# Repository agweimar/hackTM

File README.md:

# HackTM 2018 project #smucl

[Hardware overview](#hardware)

[Quickstart](#quickstart)

[Micropython](#mpython)

## Hardware overview 
The sensor board/shield holds three major components, namely:
* ESP32 breakout board with LoRa antenna and OLED display
* Flex Cable including I2C addressable Sensirion SHTC01 (rel. humidity and temperature) and SGP30 (multipixle gas sensor)
* Passive infrared sensor (PIR) a.k.a. motion sensor

A top view of the board is shown below:

### ESP32 development board 

The ESP32 breakout board is put in the socket on the lower left of the board. The usb port is facing outwards, so the board can be powered from an external (USB) power supply.
On the bottom side of the ESP32 board a small LiPo battery can be connected. Charging this battery takes place via the USB port.  
_Caution_: When booting or running the board the LoRa antenna must be connected!  
[Schematic](https://download.bastelgarage.ch/Datasheet/WIFI_LoRa_32_868_Schema.png)
[Pinout](https://download.bastelgarage.ch/Datasheet/WIFI_LoRa_32_Pinout.pdf)

### Flex cable  
The flex cable is put in the FFC socket above the ESP32 board. It is to be mounted in such a fashion, that the sensors face upwards when the cable is bent to the right (parallel to the ESP32 board).  
The flex cable combines the Sensirion SHTC1 and SGP30. Both of the sensors are accessed via I2C. The former is a sensor for relative humidity and temperature, the latter a multipixle gas sensor.  
For both sensors a convenient micropython driver can be found in the micropython directory. 

#### SGP30  
The SGP30 can give raw readings corresponding to an Ethanol (EtOH) and Hydrogen (H2) signal. However, this chip can do more! If an In-Air-Qualitiy measurement has been initialized, the raw signals are used to calculate  
the a TVOC signal (total volatile organic compounds) and an CO2 equivalent (CO2eq). These values already underly a dynamic baseline correction performed on-chip. To ensure these corrections works properly, it is advised to perform an iaq measurement once per second.  
The power consumption of the chip can be drastically minimized by soft resetting it. This is done by an i2c general call. Caution is adviced, since other i2c devices might respont to this call as well. After each reset (hard or soft) the sensor starts in idle or sleep mode with lower power consumption. If a new iaq measurement is of intereset it needs to be initialized first,
otherwise the default values are CO2eq = 400 and TVOC = 0.  
For additional information see the below datasheet.  
[SGP30 Datasheet](https://www.sensirion.com/fileadmin/user_upload/customers/sensirion/Dokumente/0_Datasheets/Gas/Sensirion_Gas_Sensors_SGP30_Datasheet.pdf)  

#### SHTC1  
The SHTC1 sensor is a little simpler than the SGP30. It gives values for temperature and relative humidity. The sensor can be soft reseted, but doesn't have a sleep mode due to its already low power consumption.
[SHTC1 Datasheet](https://www.sensirion.com/fileadmin/user_upload/customers/sensirion/Dokumente/0_Datasheets/Humidity/Sensirion_Humidity_Sensors_SHTC1_Datasheet.pdf)  
Side note: The Sensirion sensors are powered with 1.8V. The electrical components taking care of voltage generation and conversion (for the I2C bus, including 10k pull-up resistors) are situated on the bottom side of the sensor board - see picture below:

### PIR
The PIR sensor is placed on the right side of the sensor board. It produces a digital Signal (logic high) whenever a motion was detected. The sensor is internally powered by 3.3V. This voltage is generated on the PIR board by a voltage regulator.
The solder jumper labeled 'V_In' on the right side selects the input voltage - either 5V or 3.3V. Keep in mind that the 5V is only 'stable' when powered via USB.
Another (prefered and thus default) way to power the PIR Board is the second socket strip on the lower side. Originally those pins are designed to select the trigger mode (explained later). However, the outer two pins are connected to ground and 3.3V of the PIR sensor.
This enables the option to surpass the PIR's voltage regulator and save energy by directly supplying 3.3V.  
Via the solder jumpers labelled 'Single Trigger' and 'Retrigger' it can be selected if retriggering is possible. Retriggering is the possibility of increasing the duration of the digital output signal, when additional motion(s) are detected.
If 'Single Trigger' is selected the output signal will return to its default state () when a certain time has passed after detecting the first motion. Only now new motions cann trigger the sensor. The pulse length of the output signal can be selected with the left (when mounted upper) trimmable potentiometer.
The right (when mounted lower) potentiometer adjusts the sensitivity of the PIR sensor.  
[Example Datasheet](https://www.mpja.com/download/31227sc.pdf)
[Trigger Explanation](http://www.ladyada.net/media/sensors/BISS0001.pdf)

## Extras  
In addition to the previously mentioned features extra pins can be found on the sensor board. These are broken out pins (as well as solder eyelets) to conveniently expand the board.
They include the power pins (5V, 3.3V and GND - 5V may be limited to USB use) as well as the I2C pins SDA and SCL (3.3V level). Furthermore 4 GPIOs are broken out. Those can be used for a wide variety of scenarios.
All of them can be configured via software to be digital or analogue for different I/O devices. These pins could also be used as an SPI bus.

## Quickstart ESP32  

The ESP32 can be programmed using the Ardunio IDE, the Internet-of-Things Framework from Espressif or using [Micropython](https://micropython.org/). We chose Micropython, because it is very easy to start with and the code is very readable even for coders that are new to python.
Of course you can use your favourite IDE or even a simple text editor to code. However, below are a few suggestions of tools, that could make your life much easier.  

## Micropython  
In order to start with changing the sources for your needs, start looking in [micropython](micropython)

You can copy files to and from the board using different libaries:

### mpy utils  
[mpy-utils](https://github.com/nickzoic/mpy-utils) establishes a Filesystem in userspace connection to the board and allow you to change files directly on the board. (very handy)bla
_doesn't work on Windows_

### ampy
[ampy](https://github.com/adafruit/ampy) is used to interact with your esp32 board via serial connection.

### Atom with Pymakr Plugin
[Atom](https://atom.io/) can be used with the Pymakr Plugin (see [here](https://docs.pycom.io/chapter/pymakr/installation/atom.html) for help). Now you can use the powerful REPL (_Read-Evaluate-Print-Loop_),
which greatly helps while debubbing or prototyping. You can also run a pre-written script with just a click of a button (without uploading first).

### esptool.py
[esptool](https://github.com/espressif/esptool) is needed for flashing your esp32 with new firmware.

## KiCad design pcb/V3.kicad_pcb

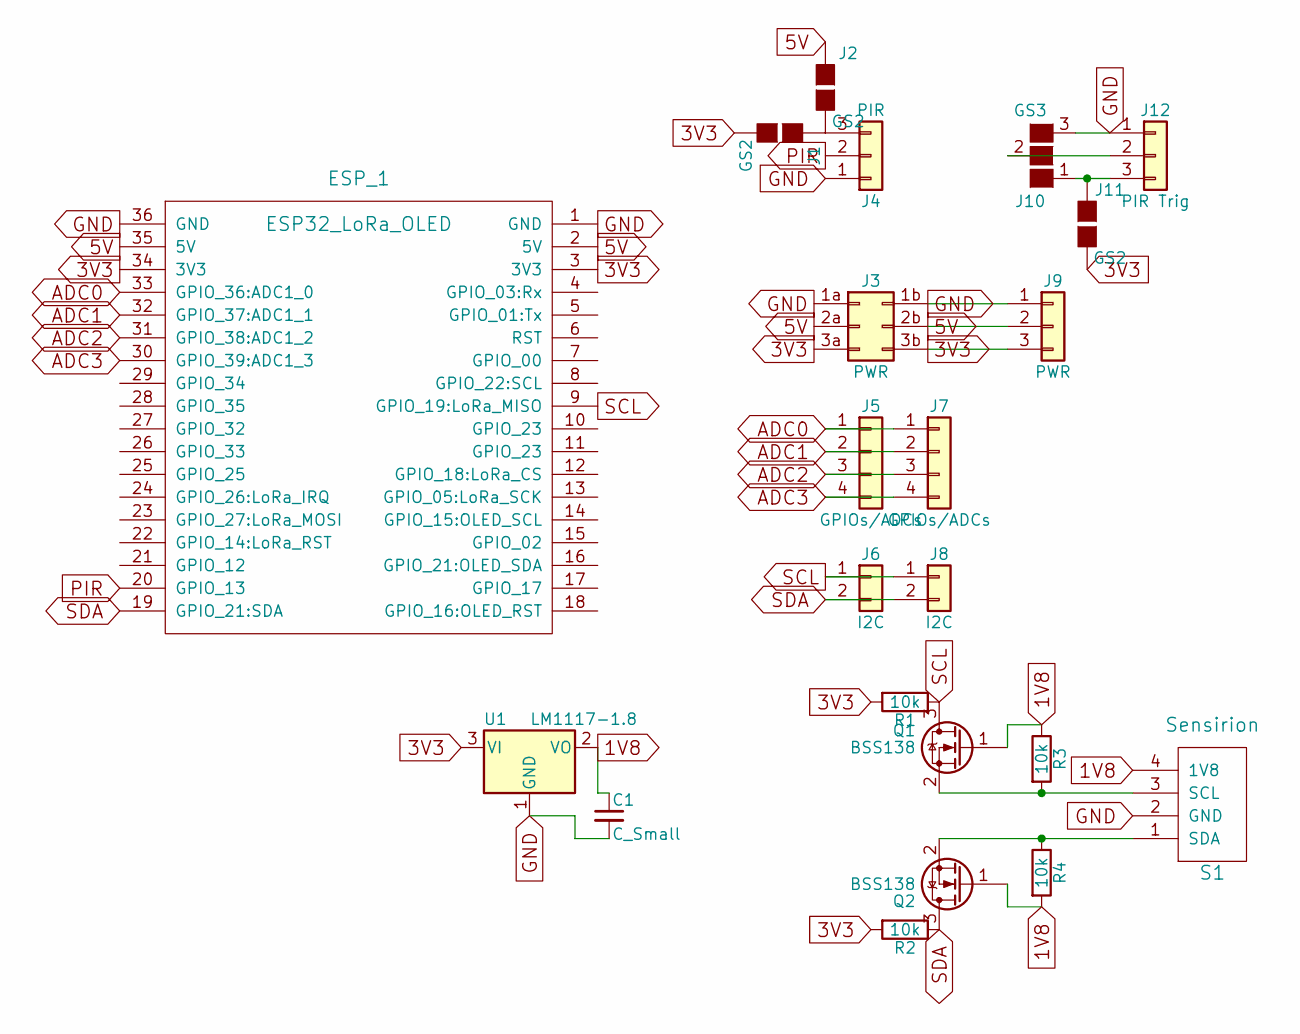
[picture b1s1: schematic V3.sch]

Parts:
C1: C_Small; C_1206_HandSoldering
ESP_1: ESP32_LoRa_OLED; ESP32_LoRa
J1, J2, J11: GS2
J3: PWR
J4: PIR; Pin_Header_Straight_1x03_Pitch2.54mm
J5, J7: GPIOs/ADCs; Pin_Header_Straight_1x04_Pitch2.54mm
J6, J8: I2C; Pin_Header_Straight_1x02_Pitch2.54mm
J9: PWR; Pin_Header_Straight_1x03_Pitch2.54mm
J10: GS3
J12: PIR Trig; Pin_Header_Straight_1x03_Pitch2.54mm
Q1, Q2: BSS138; SOT-23_Handsoldering
R1, R2, R3, R4: 10k; R_1206_HandSoldering
S1: Sensirion; FFC Amphenol
U1: LM1117-1.8; SOT-223-3_TabPin2

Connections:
1V8: C1.1, Q1.1 (G), Q2.1 (G), R3.1, R4.2, S1.4 (1V8), U1.2 (VO)
3V3: ESP_1.3 (3V3), ESP_1.34 (3V3), J1.2 (G2), J3.3a, J3.3b, J9.3, J11.2 (G2), R1.2, R2.2, U1.3 (VI)
5V: ESP_1.2 (5V), ESP_1.35 (5V), J2.1 (G1), J3.2a, J3.2b, J9.2
ADC0: ESP_1.33 (GPIO_36:ADC1_0), J5.1, J7.1
ADC1: ESP_1.32 (GPIO_37:ADC1_1), J5.2, J7.2
ADC2: ESP_1.31 (GPIO_38:ADC1_2), J5.3, J7.3
ADC3: ESP_1.30 (GPIO_39:ADC1_3), J5.4, J7.4
GND: C1.2, ESP_1.1 (GND), ESP_1.36 (GND), J3.1a, J3.1b, J4.1, J9.1, J10.3 (G3), J12.1, S1.2 (GND), U1.1 (GND)
unnamed: J1.1 (G1), J2.2 (G2), J4.3
unnamed: J10.1 (G1), J11.1 (G1), J12.3
unnamed: J10.2 (G2), J12.2
unnamed: Q1.2 (S), R3.2, S1.3 (SCL)
unnamed: Q2.2 (S), R4.1, S1.1 (SDA)
PIR: ESP_1.20 (GPIO_13), J4.2
SCL: ESP_1.9 (GPIO_19:LoRa_MISO), J6.1, J8.1, Q1.3 (D), R1.1
SDA: ESP_1.19 (GPIO_21:SDA), J6.2, J8.2, Q2.3 (D), R2.1

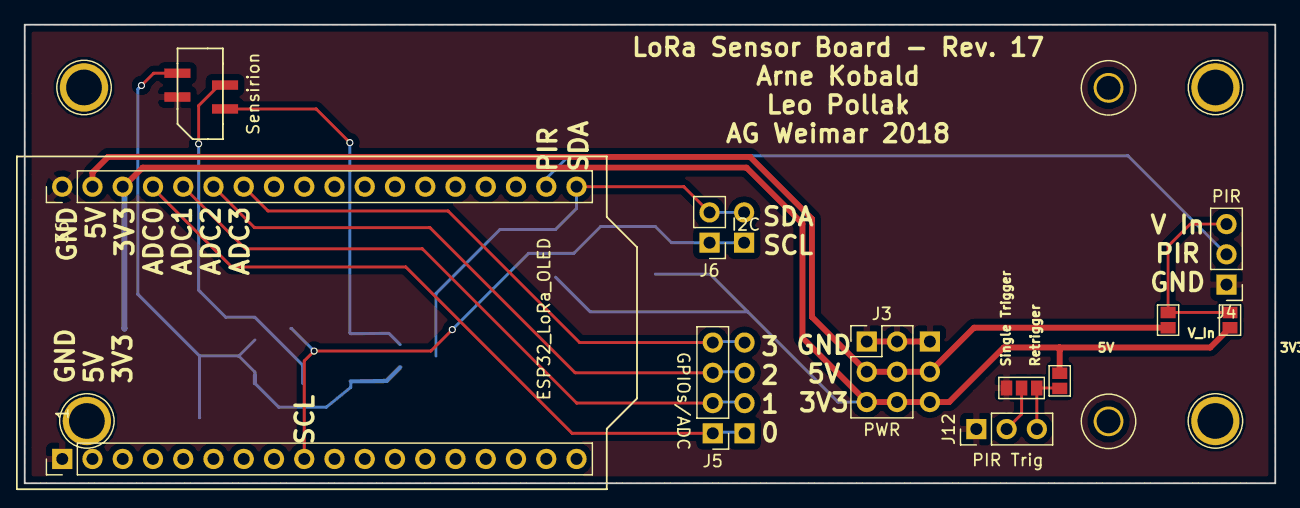
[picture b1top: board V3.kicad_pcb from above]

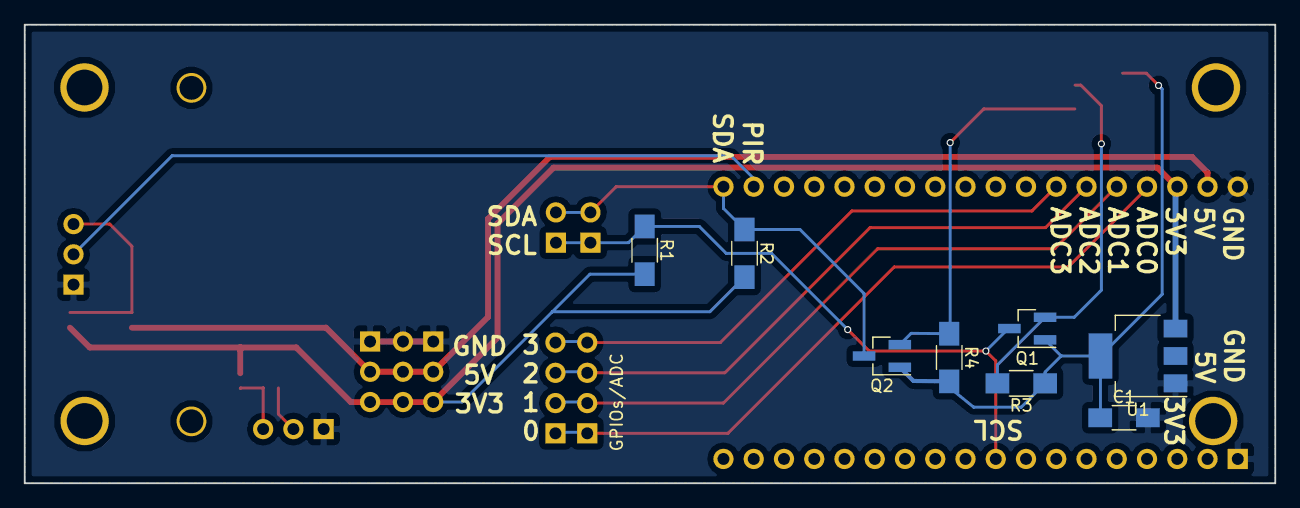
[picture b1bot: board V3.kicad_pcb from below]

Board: 2 copper layers, 105.0 x 38.5 mm, 22 parts (8 on the bottom side), 16 nets.

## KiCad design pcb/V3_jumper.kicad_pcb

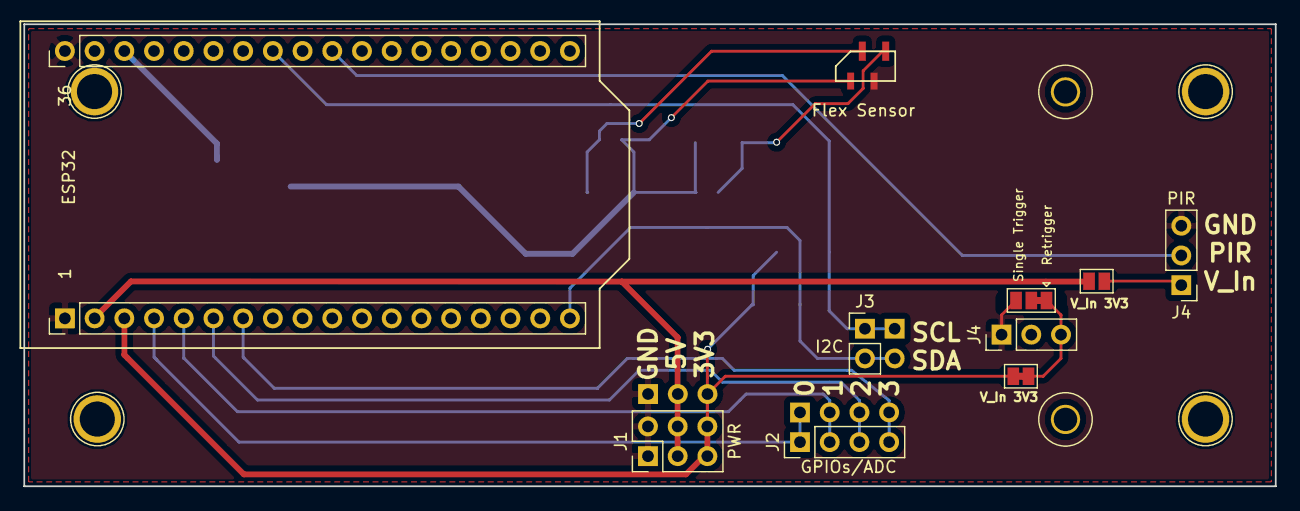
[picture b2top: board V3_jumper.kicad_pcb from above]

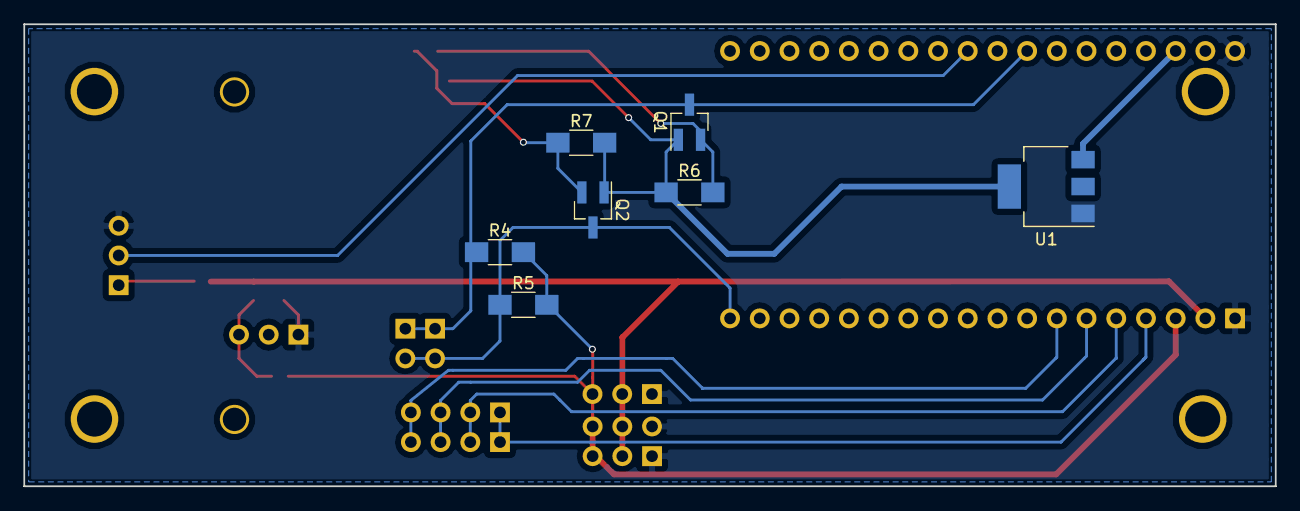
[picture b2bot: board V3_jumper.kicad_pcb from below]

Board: 2 copper layers, 107.0 x 39.5 mm, 14 parts (7 on the bottom side), 13 nets.

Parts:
ESP32: ESP32_LoRa_OLED; ESP32_LoRa
Flex Sensor: Sensirion; FFC Molex
J1: PWR
J2: Pin_Header_Straight_1x04_Pitch2.54mm
J3: I2C; Pin_Header_Straight_1x02_Pitch2.54mm
J4: Pin_Header_Straight_1x03_Pitch2.54mm
J4#2: PIR; Pin_Header_Straight_1x03_Pitch2.54mm
Q1, Q2: BSS138; SOT-23_Handsoldering
R4, R5, R6, R7: 10k; R_1206_HandSoldering
U1: LM1117-1.8; SOT-223-3_TabPin2

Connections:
1V8: Flex Sensor.1, Q1.1, Q2.1, R6.1, R7.2, U1.2
3V3: ESP32.3, ESP32.34, J1.3a, J1.3b, R4.2, R5.2, U1.3
5V: ESP32.2, ESP32.35, J1.2a, J1.2b
ADC0: ESP32.4, J2.1
ADC1: ESP32.5, J2.2
ADC2: ESP32.6, J2.3
ADC3: ESP32.7, J2.4
GND: ESP32.1, ESP32.36, Flex Sensor.3, J1.1a, J1.1b, J4.1, J4#2.3, U1.1
unnamed: Flex Sensor.2, Q1.2, R6.2
unnamed: Flex Sensor.4, Q2.2, R7.1
PIR: ESP32.27, J4#2.2
SCL: ESP32.29, J3.1, Q1.3, R4.1
SDA: ESP32.18, J3.2, Q2.3, R5.1

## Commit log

2018-04-12 hackTM folder added
2018-04-12 removed hackTM folder
2018-04-12 added hackTM folder
2018-04-12 mp update
2018-04-12 readme
2018-04-12 bugfix
2018-04-15 update readme-hardware
2018-04-16 add Quickstart info for ESP32 / micropython
2018-04-19 sensor data via lora
2018-04-23 test commit
2018-04-24 Update README.md Links instead of Docs
2018-04-26 test_board_3 updated
2018-04-26 Update SHTC1.py soft reset
2018-04-27 uart
2018-04-29 new test_board version - code refactor
2018-04-30 packlisten
2018-05-02 loboris compatibility
2018-05-03 smartpi code updated
2018-05-04 cleanup
2018-05-04 added license
2018-05-08 sgp on-off-timing
2018-05-08 LoBo firmware rebuild with sgp30 driver update
2018-05-08 controller fix
2018-05-09 MP readme update
2018-05-09 updated mp firmware
2018-05-09 fw fixing
2018-05-09 asdf
2018-05-09 readme update
2018-05-09 sgp eco_mode
2018-05-09 updating
2018-05-11 deepsleep, Button0
2018-05-12 payload data
2018-05-12 offline
2018-05-12 offline lora flag
2018-05-12 added data from continental city tour
2018-05-12 whoops
2018-05-13 added test drive protocol
2018-05-13 version smartpi
2018-05-13 update info
2018-05-13 header
2018-05-13 changed defaults for higher tx power
2018-05-13 add frequencies for all LoRa channels
2018-05-13 fix +=
2018-05-13 range test list
2018-05-13 drone
2018-05-16 Update README.md
    Added index and more info
2018-05-17 updated MP documentation
2018-05-17 skeleton update
2018-05-25 Add fail info for menuconfig
2018-05-25 whitespace cleanup
2018-05-25 fixed import
2018-05-25 fixed lora frequency
2018-05-25 actually do something
2018-07-10 working as intended
2018-07-20 removed sgp sleep mode
